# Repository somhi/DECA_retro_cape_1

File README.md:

# Arrow DECA Retro Cape 1 (4 layer - embedded SDRAM - Edge connector)

**STATUS (10/03/22):  prototype design work in progress**

Project has been developed with KiCAD 6.0. 

All credits for SDRAM design goes to Tom Verbeure from whom I've taken his [original design  files](https://github.com/tomverbeure/arrow_deca_retro_cape) and adapted to my own design.

As I already developed an Edge to Pmod PCB, I'll be using here attached to the DECA cape. See details at https://github.com/somhi/MIDI_I2S_SBC_Pmod_Edge_Interface

### **Schematic**

 [arrow_deca_retro_cape.pdf](arrow_deca_retro_cape.pdf) 

### **Features**

* 

### 3D model

### **Additional notes**

* 

### **Jumper Selection**

* 

### Changelog

v0.5  routed finalized

v0.6  embedded SDRAM version only. External Mister module removed in order to improve signal integrity.

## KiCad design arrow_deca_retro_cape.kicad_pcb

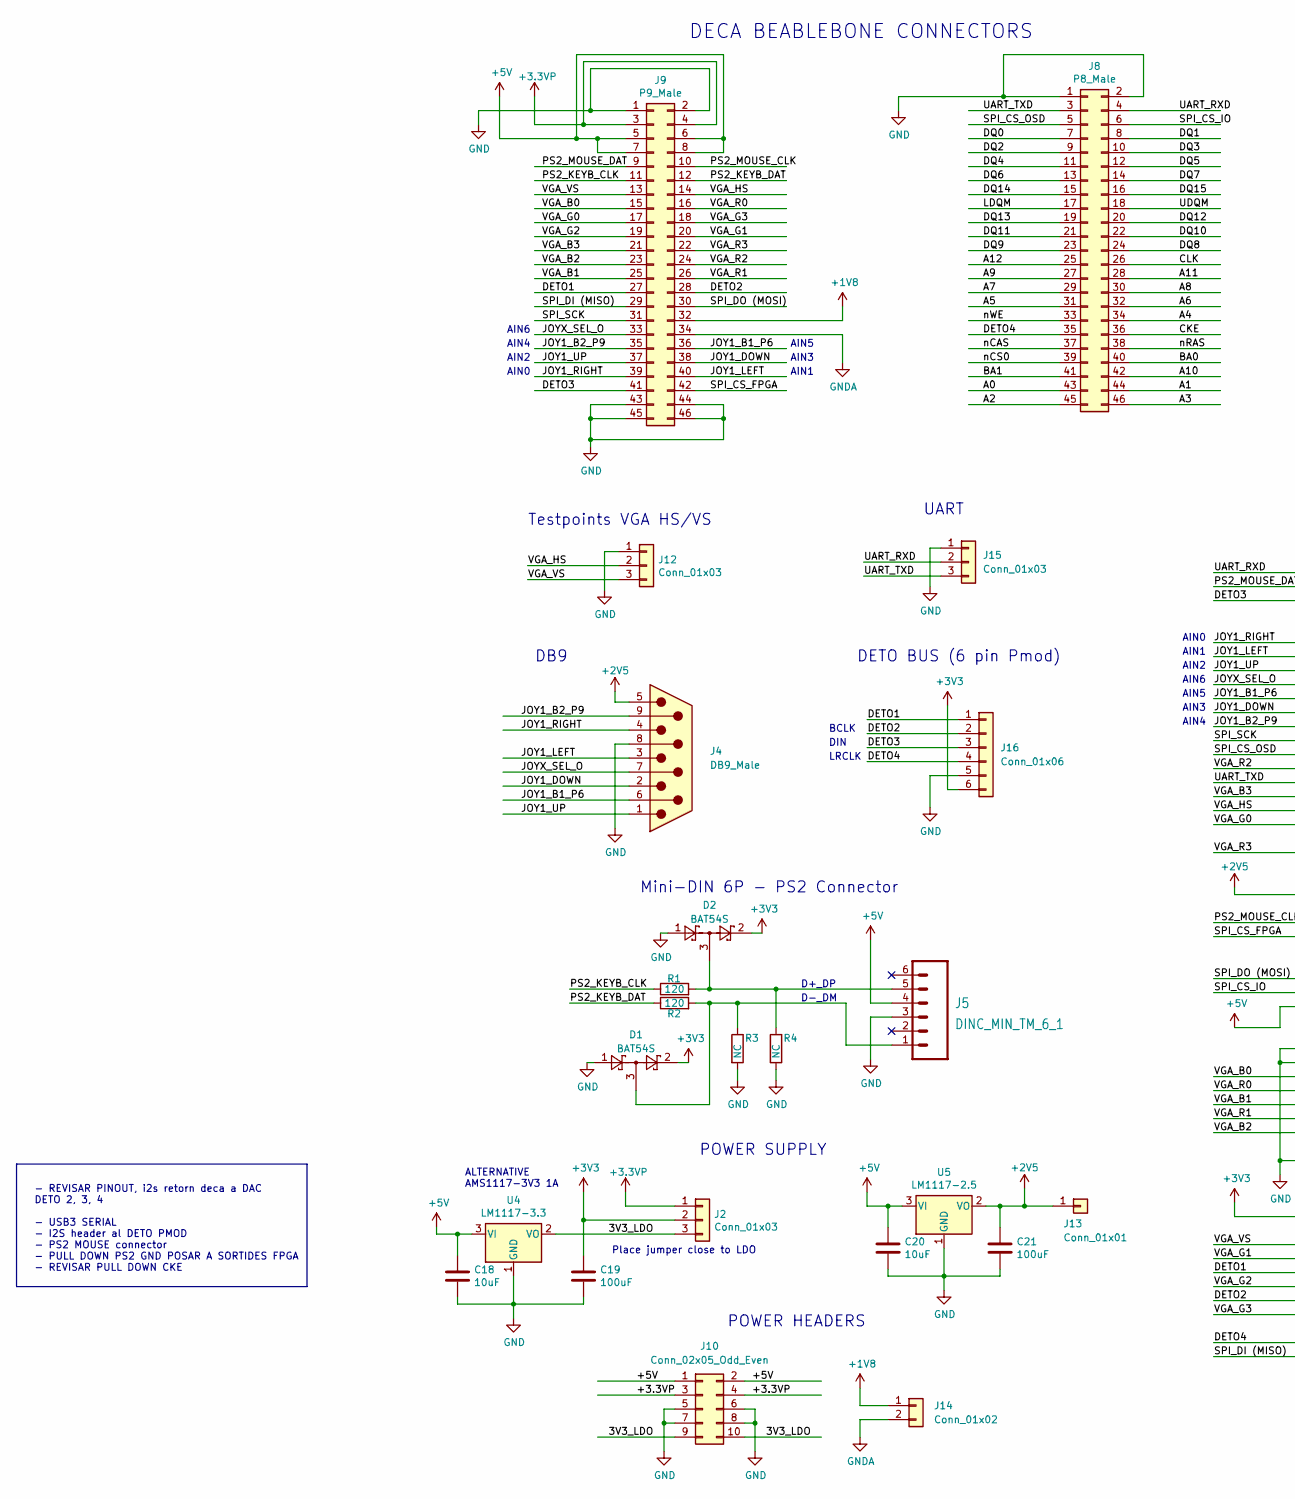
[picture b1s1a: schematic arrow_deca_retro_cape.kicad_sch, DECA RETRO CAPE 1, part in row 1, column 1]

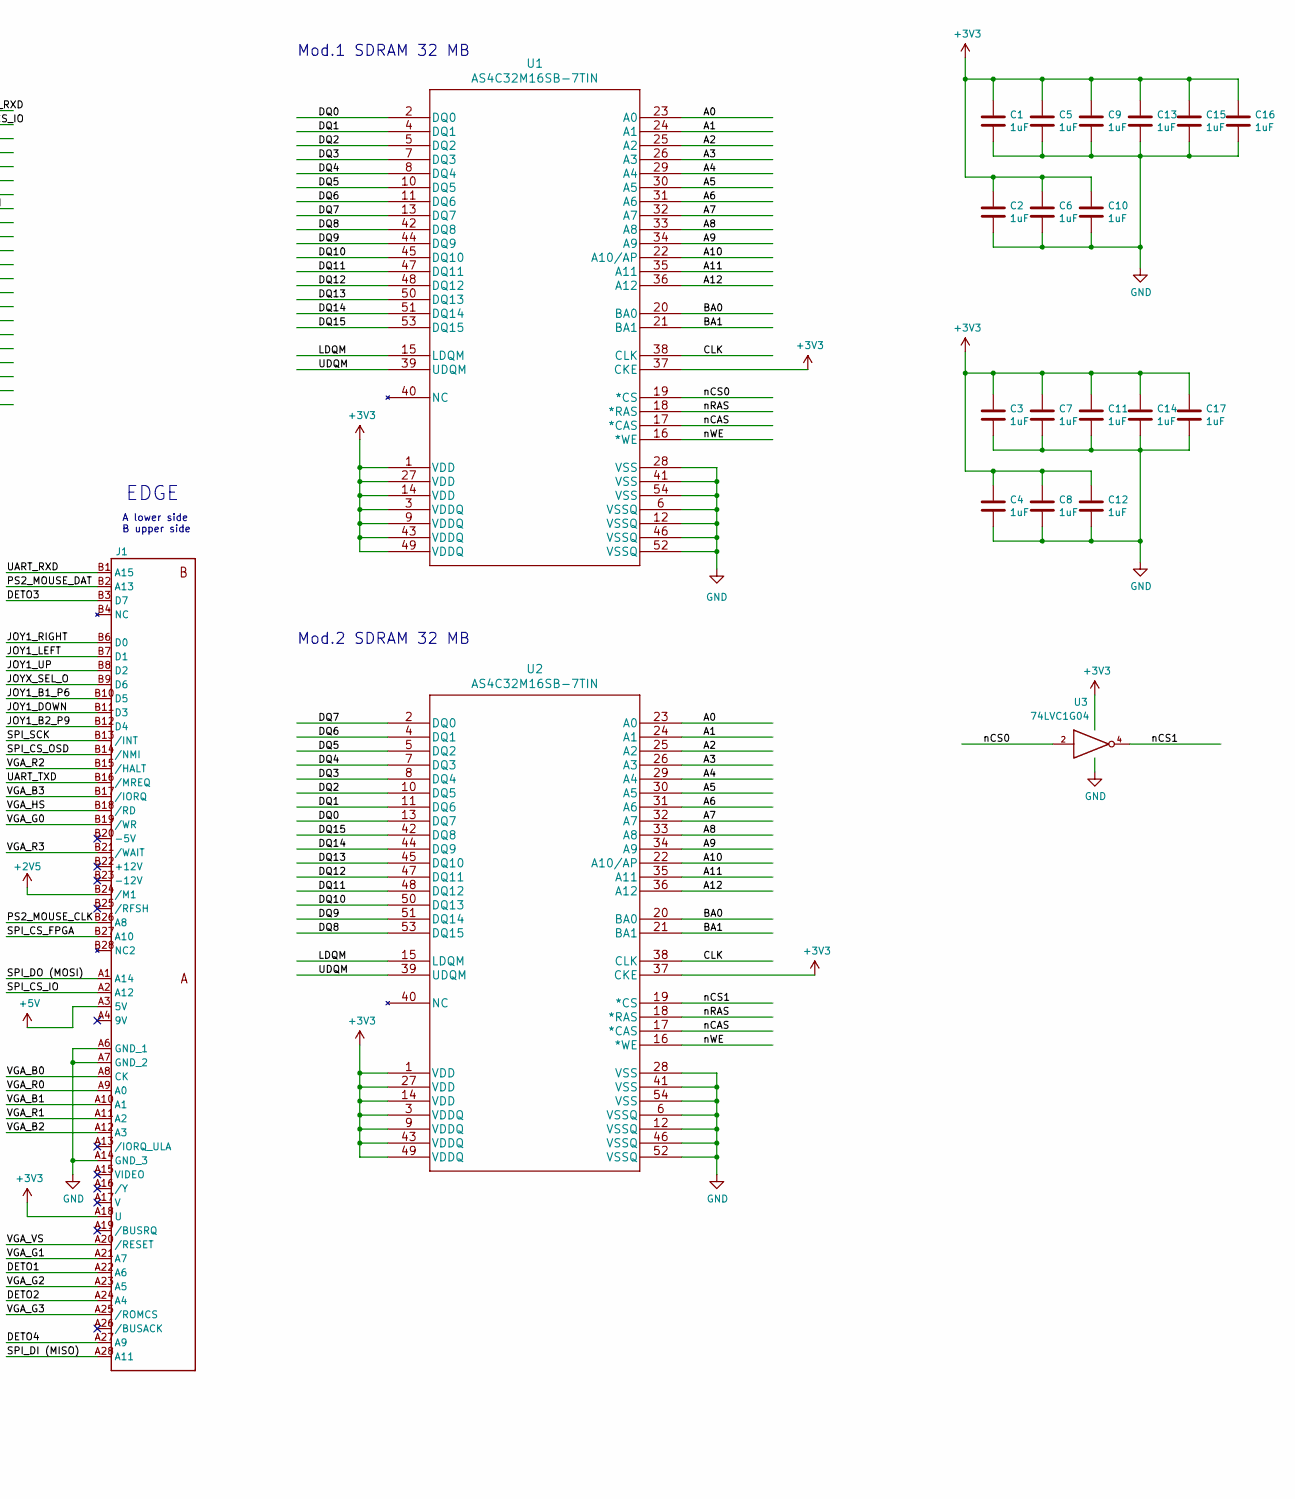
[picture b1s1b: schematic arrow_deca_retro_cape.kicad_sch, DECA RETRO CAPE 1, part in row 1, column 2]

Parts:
C1, C2, C3, C4, C5, C6, C7, C8, C9, C10, C11, C12, C13, C14, C15, C16, C17: 1uF; C_0603_1608Metric_Pad1.05x0.95mm_HandSolder
C18: 10uF; C_0805_2012Metric_Pad1.15x1.40mm_HandSolder
C19: 100uF; C_0805_2012Metric_Pad1.15x1.40mm_HandSolder
C20: 10uF; C_0805_2012Metric_Pad1.18x1.45mm_HandSolder
C21: 100uF; C_0805_2012Metric_Pad1.18x1.45mm_HandSolder
D1, D2: BAT54S; SOT-23
J1: ZXSP_ED2X28_SPE_SOL_EDGE; 2X28_SPE2
J2, J12, J15: Conn_01x03; PinHeader_1x03_P2.54mm_Vertical
J4: DB9_Male; DSUB-9_Male_Horizontal_P2.77x2.84mm_EdgePinOffset9.90mm_Hou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
J5: DINC_MIN_TM_6_1; DINC_MIN_TM_6_1PRIMARY
J8: P8_Male; PinHeader_2x23_P2.54mm_Vertical
J9: P9_Male; PinHeader_2x23_P2.54mm_Vertical
J10: Conn_02x05_Odd_Even; PinSocket_2x05_P2.54mm_Vertical
J13: Conn_01x01; PinSocket_1x01_P2.54mm_Vertical
J14: Conn_01x02; PinSocket_1x02_P2.54mm_Vertical
J16: Conn_01x06; PinHeader_1x06_P2.54mm_Vertical
R1, R2: 120; R_0805_2012Metric_Pad1.20x1.40mm_HandSolder
R3, R4: NC; R_0805_2012Metric_Pad1.20x1.40mm_HandSolder
U1, U2: AS4C32M16SB-7TIN
U3: 74LVC1G04; SOT-23-5
U4: LM1117-3.3; SOT-223-3_TabPin2
U5: LM1117-2.5; SOT-223-3_TabPin2

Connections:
+1V8: J9.32, J14.1
+2V5: C21.1, J1.B24 (/M1), J4.5, J13.1, U5.2 (VO)
+3.3VP: J2.1, J9.3, J9.4, J10.3, J10.4
+3V3: C1.1, C2.1, C3.1, C4.1, C5.1, C6.1, C7.1, C8.1, C9.1, C10.1, C11.1, C12.1, C13.1, C14.1, C15.1, C16.1, C17.1, C19.1, D1.2, D2.2, J1.A18 (U), J2.2, J16.6, U1.1 (VDD), U1.3 (VDDQ), U1.9 (VDDQ), U1.14 (VDD), U1.27 (VDD), U1.37 (CKE), U1.43 (VDDQ), U1.49 (VDDQ), U2.1 (VDD), U2.3 (VDDQ), U2.9 (VDDQ), U2.14 (VDD), U2.27 (VDD), U2.37 (CKE), U2.43 (VDDQ), U2.49 (VDDQ), U3.5 (VCC)
+5V: C18.1, C20.1, J1.A3 (5V), J5.4, J9.5, J9.6, J9.7, J9.8, J10.1, J10.2, U4.3 (VI), U5.3 (VI)
/3V3_LDO: J2.3, J10.9, J10.10, U4.2 (VO)
/A0: J8.43, U1.23 (A0), U2.23 (A0)
/A1: J8.44, U1.24 (A1), U2.24 (A1)
/A2: J8.45, U1.25 (A2), U2.25 (A2)
/A3: J8.46, U1.26 (A3), U2.26 (A3)
/A4: J8.34, U1.29 (A4), U2.29 (A4)
/A5: J8.31, U1.30 (A5), U2.30 (A5)
/A6: J8.32, U1.31 (A6), U2.31 (A6)
/A7: J8.29, U1.32 (A7), U2.32 (A7)
/A8: J8.30, U1.33 (A8), U2.33 (A8)
/A9: J8.27, U1.34 (A9), U2.34 (A9)
/A10: J8.42, U1.22 (A10/AP), U2.22 (A10/AP)
/A11: J8.28, U1.35 (A11), U2.35 (A11)
/A12: J8.25, U1.36 (A12), U2.36 (A12)
/BA0: J8.40, U1.20 (BA0), U2.20 (BA0)
/BA1: J8.41, U1.21 (BA1), U2.21 (BA1)
/CKE: J8.36
/CLK: J8.26, U1.38 (CLK), U2.38 (CLK)
/DETO1: J1.A22 (A6), J9.27, J16.1
/DETO2: J1.A24 (A4), J9.28, J16.2
/DETO3: J1.B3 (D7), J9.41, J16.3
/DETO4: J1.A27 (A9), J8.35, J16.4
/DQ0: J8.7, U1.2 (DQ0), U2.13 (DQ7)
/DQ1: J8.8, U1.4 (DQ1), U2.11 (DQ6)
/DQ2: J8.9, U1.5 (DQ2), U2.10 (DQ5)
/DQ3: J8.10, U1.7 (DQ3), U2.8 (DQ4)
/DQ4: J8.11, U1.8 (DQ4), U2.7 (DQ3)
/DQ5: J8.12, U1.10 (DQ5), U2.5 (DQ2)
/DQ6: J8.13, U1.11 (DQ6), U2.4 (DQ1)
/DQ7: J8.14, U1.13 (DQ7), U2.2 (DQ0)
/DQ8: J8.24, U1.42 (DQ8), U2.53 (DQ15)
/DQ9: J8.23, U1.44 (DQ9), U2.51 (DQ14)
/DQ10: J8.22, U1.45 (DQ10), U2.50 (DQ13)
/DQ11: J8.21, U1.47 (DQ11), U2.48 (DQ12)
/DQ12: J8.20, U1.48 (DQ12), U2.47 (DQ11)
/DQ13: J8.19, U1.50 (DQ13), U2.45 (DQ10)
/DQ14: J8.15, U1.51 (DQ14), U2.44 (DQ9)
/DQ15: J8.16, U1.53 (DQ15), U2.42 (DQ8)
/JOY1_B1_P6: J1.B10 (D5), J4.6, J9.36
/JOY1_B2_P9: J1.B12 (D4), J4.9, J9.35
/JOY1_DOWN: J1.B11 (D3), J4.2, J9.38
/JOY1_LEFT: J1.B7 (D1), J4.3, J9.40
/JOY1_RIGHT: J1.B6 (D0), J4.4, J9.39
/JOY1_UP: J1.B8 (D2), J4.1, J9.37
/JOYX_SEL_O: J1.B9 (D6), J4.7, J9.33
/LDQM: J8.17, U1.15 (LDQM), U2.15 (LDQM)
/PS2_KEYB_CLK: J9.11, R1.1
/PS2_KEYB_DAT: J9.12, R2.1
/PS2_MOUSE_CLK: J1.B26 (A8), J9.10
/PS2_MOUSE_DAT: J1.B2 (A13), J9.9
/SPI_CS_FPGA: J1.B27 (A10), J9.42
/SPI_CS_IO: J1.A2 (A12), J8.6
/SPI_CS_OSD: J1.B14 (/NMI), J8.5
/SPI_DI (MISO): J1.A28 (A11), J9.29
/SPI_DO (MOSI): J1.A1 (A14), J9.30
/SPI_SCK: J1.B13 (/INT), J9.31
/UART_RXD: J1.B1 (A15), J8.4, J15.2
/UART_TXD: J1.B16 (/MREQ), J8.3, J15.3
/UDQM: J8.18, U1.39 (UDQM), U2.39 (UDQM)
/VGA_B0: J1.A8 (CK), J9.15
/VGA_B1: J1.A10 (A1), J9.25
/VGA_B2: J1.A12 (A3), J9.23
/VGA_B3: J1.B17 (/IORQ), J9.21
/VGA_G0: J1.B19 (/WR), J9.17
/VGA_G1: J1.A21 (A7), J9.20
/VGA_G2: J1.A23 (A5), J9.19
/VGA_G3: J1.A25 (/ROMCS), J9.18
/VGA_HS: J1.B18 (/RD), J9.14, J12.2
/VGA_R0: J1.A9 (A0), J9.16
/VGA_R1: J1.A11 (A2), J9.26
/VGA_R2: J1.B15 (/HALT), J9.24
/VGA_R3: J1.B21 (/WAIT), J9.22
/VGA_VS: J1.A20 (/RESET), J9.13, J12.3
/nCAS: J8.37, U1.17 (*CAS), U2.17 (*CAS)
/nCS0: J8.39, U1.19 (*CS), U3.2
/nCS1: U2.19 (*CS), U3.4
/nRAS: J8.38, U1.18 (*RAS), U2.18 (*RAS)
/nWE: J8.33, U1.16 (*WE), U2.16 (*WE)
GND: C1.2, C2.2, C3.2, C4.2, C5.2, C6.2, C7.2, C8.2, C9.2, C10.2, C11.2, C12.2, C13.2, C14.2, C15.2, C16.2, C17.2, C18.2, C19.2, C20.2, C21.2, D1.1, D2.1, J1.A6 (GND_1), J1.A7 (GND_2), J1.A14 (GND_3), J4.8, J5.3, J8.1, J8.2, J9.1, J9.2, J9.43, J9.44, J9.45, J9.46, J10.5, J10.6, J10.7, J10.8, J12.1, J15.1, J16.5, R3.2, R4.2, U1.6 (VSSQ), U1.12 (VSSQ), U1.28 (VSS), U1.41 (VSS), U1.46 (VSSQ), U1.52 (VSSQ), U1.54 (VSS), U2.6 (VSSQ), U2.12 (VSSQ), U2.28 (VSS), U2.41 (VSS), U2.46 (VSSQ), U2.52 (VSSQ), U2.54 (VSS), U3.3 (GND), U4.1 (GND), U5.1 (GND)
GNDA: J9.34, J14.2
unnamed: D1.3, J5.1, R2.2, R3.1
unnamed: D2.3, J5.5, R1.2, R4.1

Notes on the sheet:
D-_DM
Mod.1 SDRAM 32 MB
POWER HEADERS
ALTERNATIVE AMS1117-3V3 1A
Testpoints VGA HS/VS
AIN2
BCLK
AIN6
DB9
DIN
AIN3
POWER SUPPLY
AIN1
Mod.2 SDRAM 32 MB
LRCLK
AIN5
DECA BEABLEBONE CONNECTORS
AIN0
AIN4
Place jumper close to LDO
A lower side B upper side
UART
D+_DP
Mini-DIN 6P - PS2 Connector
- REVISAR PINOUT, i2s retorn deca a DAC DETO 2, 3, 4 - USB3 SERIAL - I2S header al DETO PMOD - PS2 MOUSE connector - PULL DOWN PS2 GND POSAR A SORTIDES FPGA - REVISAR PULL DOWN CKE
DETO BUS (6 pin Pmod)
EDGE

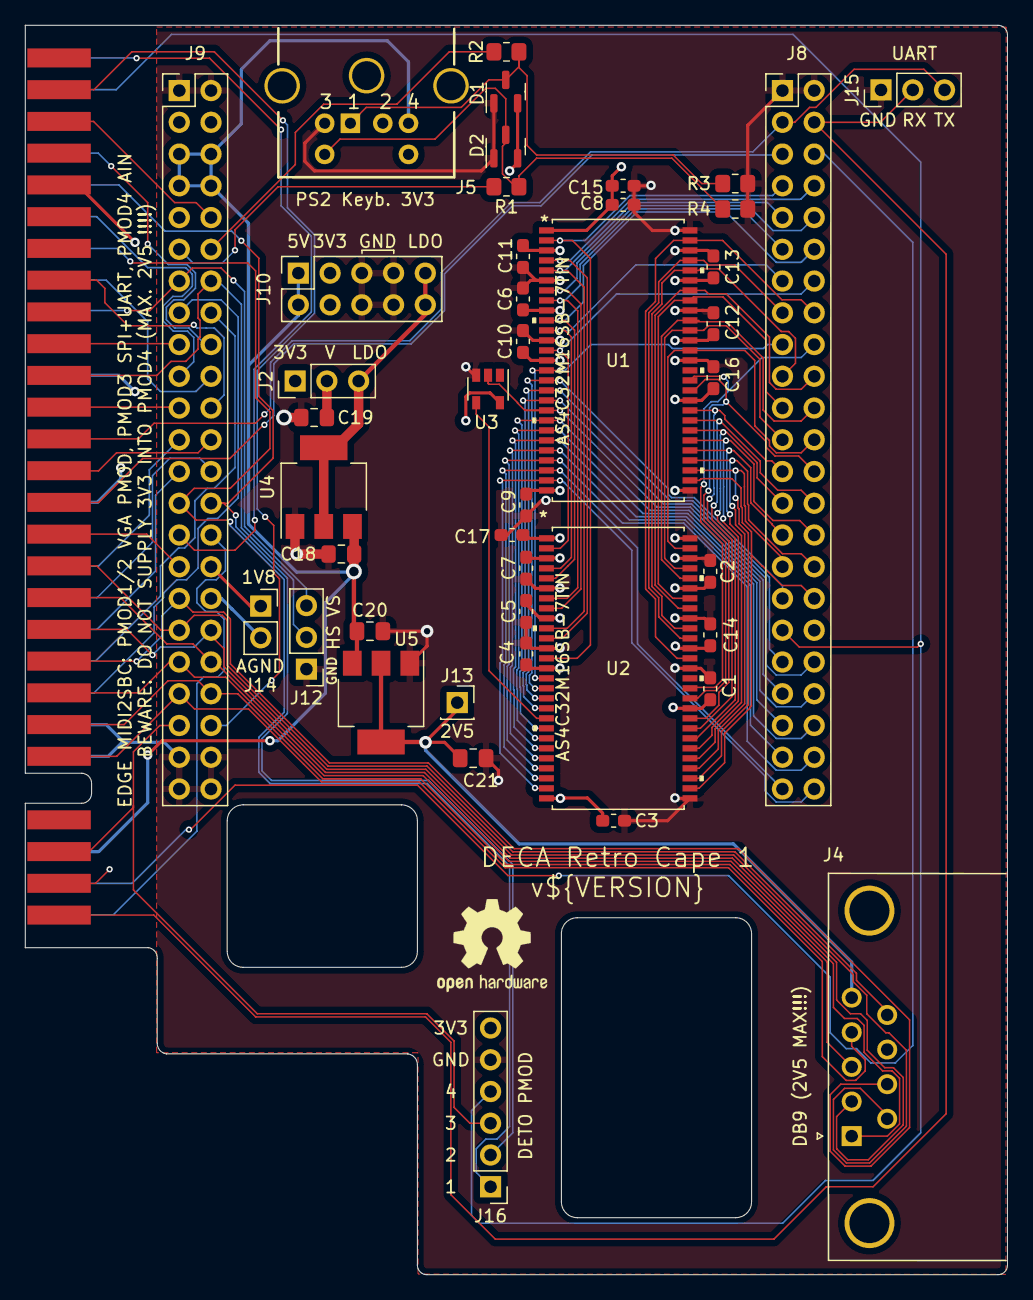
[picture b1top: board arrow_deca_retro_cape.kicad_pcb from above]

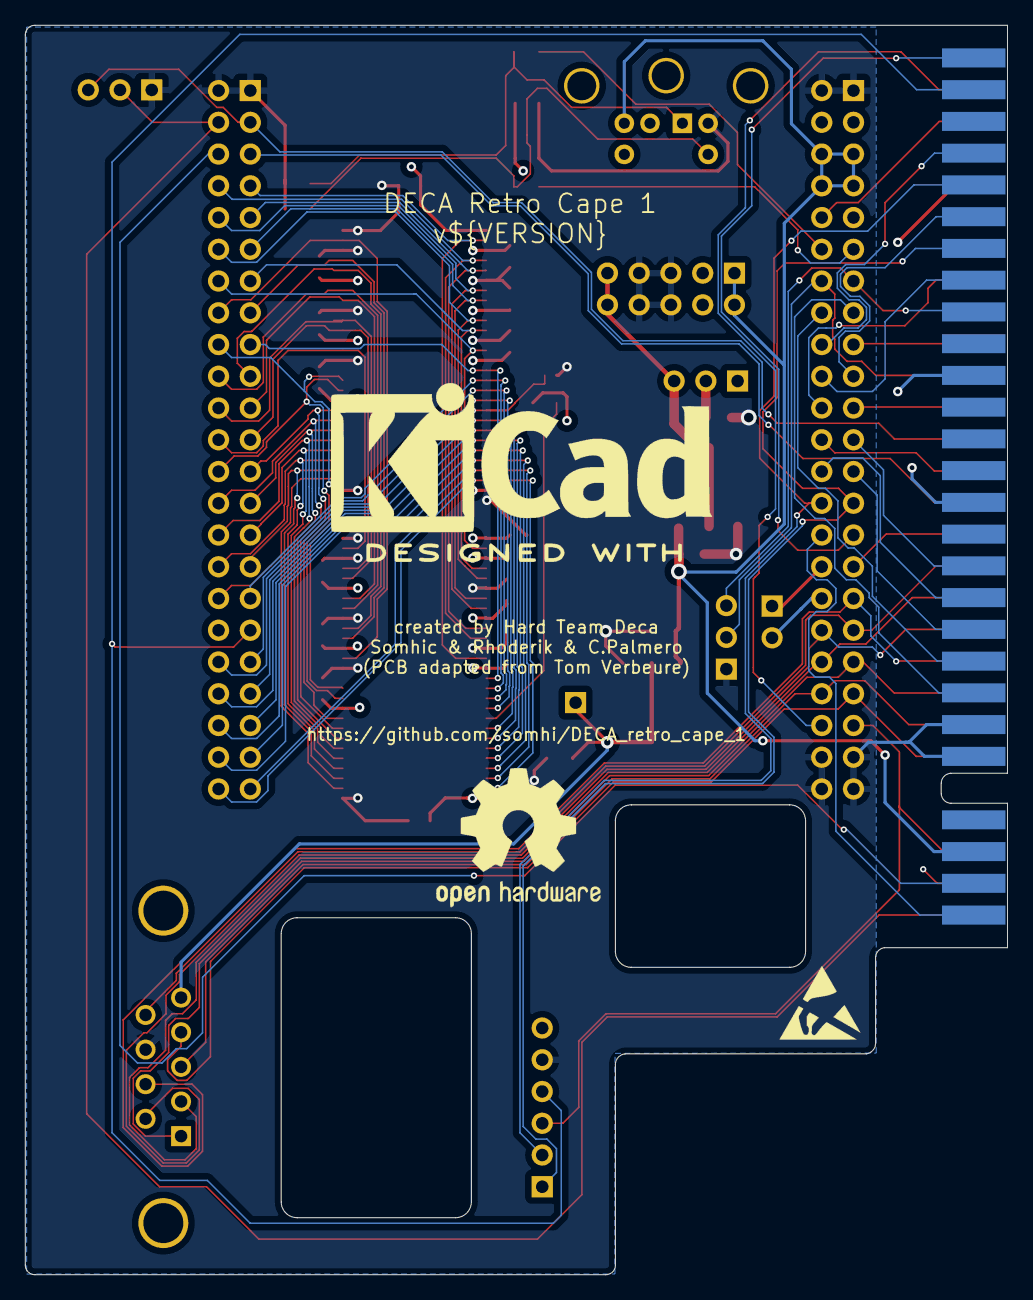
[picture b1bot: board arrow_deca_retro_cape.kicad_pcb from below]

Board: 4 copper layers, 78.6 x 100.0 mm, 48 parts (3 on the bottom side), 86 nets.

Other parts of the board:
LO1: KiCad-Logo2_12mm_SilkScreen
LO2: OSHW-Logo2_9.8x8mm_SilkScreen
LO3: OSHW-Logo2_14.6x12mm_SilkScreen
LO4: ESD-Logo_6.6x6mm_SilkScreen

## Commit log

2022-03-10 added Deto pmod
2022-03-10 cleaning
2022-03-10 v0.5 routing finalized
2022-03-11 update before split
2022-03-11 v0.6 embedded SDRAM only version

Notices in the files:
arrow_deca_retro_cape.kicad_pcb:
License: CC-BY-SA v4.0
parts and their libraries:
Copyright 2021 Accelerated Designs. All rights reserved.
